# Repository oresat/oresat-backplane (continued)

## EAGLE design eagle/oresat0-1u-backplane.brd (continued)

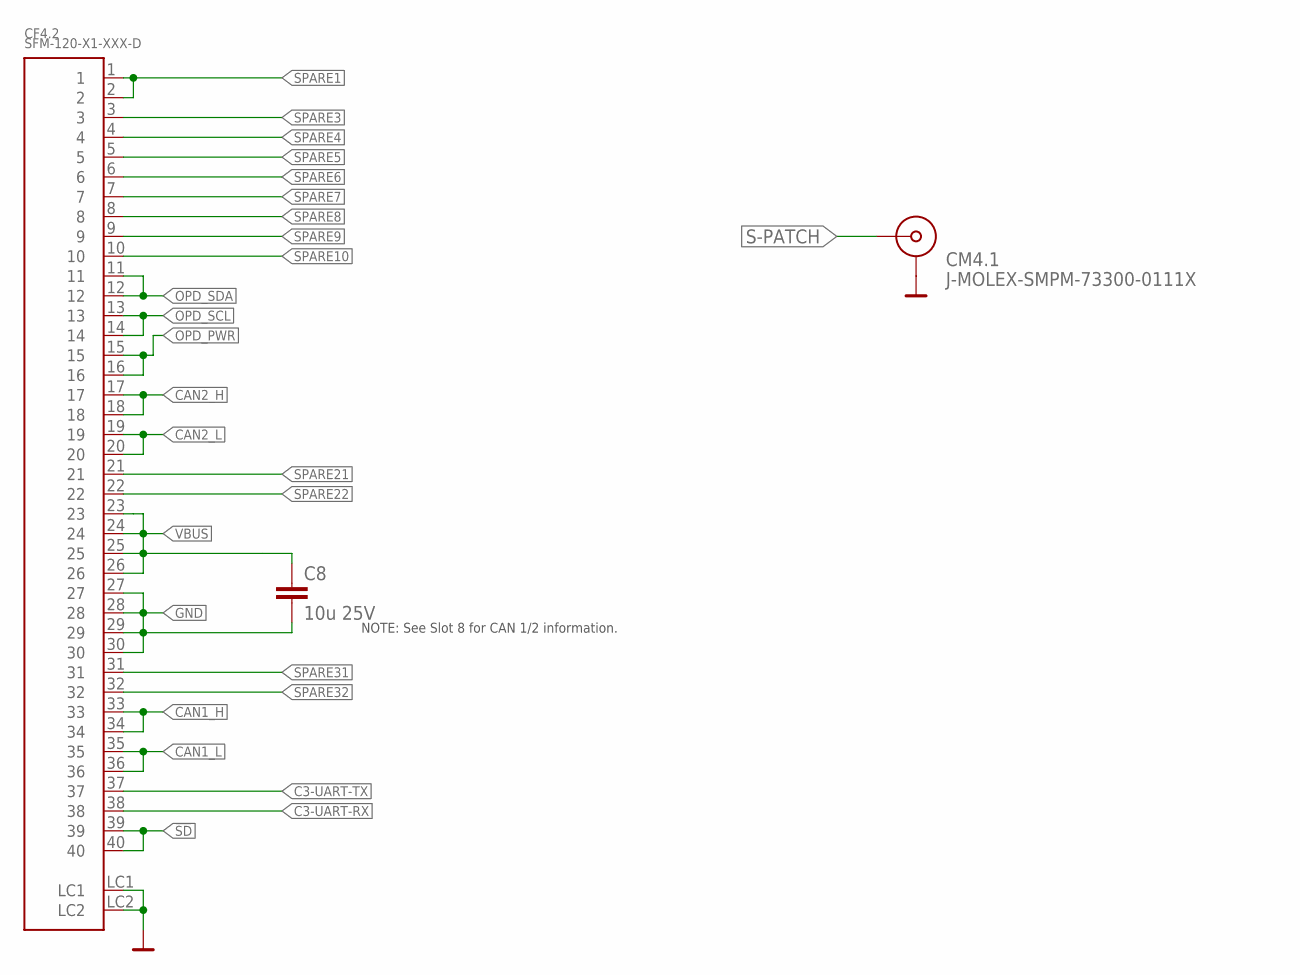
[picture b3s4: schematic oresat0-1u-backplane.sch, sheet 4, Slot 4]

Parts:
C8: 10u 25V; 1206-B
CF4.2: SFM-120-X1-XXX-D
CM4.1: J-MOLEX-SMPM-73300-0111X

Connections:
!SD: CF4.2.39, CF4.2.40; also elsewhere on the board
C3-UART-RX: CF4.2.38; also elsewhere on the board
C3-UART-TX: CF4.2.37; also elsewhere on the board
CAN1_H: CF4.2.33, CF4.2.34; also elsewhere on the board
CAN1_L: CF4.2.35, CF4.2.36; also elsewhere on the board
CAN2_H: CF4.2.17, CF4.2.18; also elsewhere on the board
CAN2_L: CF4.2.19, CF4.2.20; also elsewhere on the board
GND: C8.2, CF4.2.27, CF4.2.28, CF4.2.29, CF4.2.30, CF4.2.LC1, CF4.2.LC2, CM4.1.P$1 (SHIELD1), CM4.1.P$2 (SHIELD1), CM4.1.P$3 (SHIELD1), CM4.1.P$4 (SHIELD1); also elsewhere on the board
OPD_PWR: CF4.2.15, CF4.2.16; also elsewhere on the board
OPD_SCL: CF4.2.13, CF4.2.14; also elsewhere on the board
OPD_SDA: CF4.2.11, CF4.2.12; also elsewhere on the board
S-PATCH: CM4.1.RF-DOWN (RF); also elsewhere on the board
SPARE1: CF4.2.1, CF4.2.2; also elsewhere on the board
SPARE3: CF4.2.3; also elsewhere on the board
SPARE4: CF4.2.4; also elsewhere on the board
SPARE5: CF4.2.5; also elsewhere on the board
SPARE6: CF4.2.6; also elsewhere on the board
SPARE7: CF4.2.7; also elsewhere on the board
SPARE8: CF4.2.8; also elsewhere on the board
SPARE9: CF4.2.9; also elsewhere on the board
SPARE10: CF4.2.10; also elsewhere on the board
SPARE21: CF4.2.21; also elsewhere on the board
SPARE22: CF4.2.22; also elsewhere on the board
SPARE31: CF4.2.31; also elsewhere on the board
SPARE32: CF4.2.32; also elsewhere on the board
VBUS: C8.1, CF4.2.23, CF4.2.24, CF4.2.25, CF4.2.26; also elsewhere on the board

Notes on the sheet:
NOTE: See Slot 8 for CAN 1/2 information.

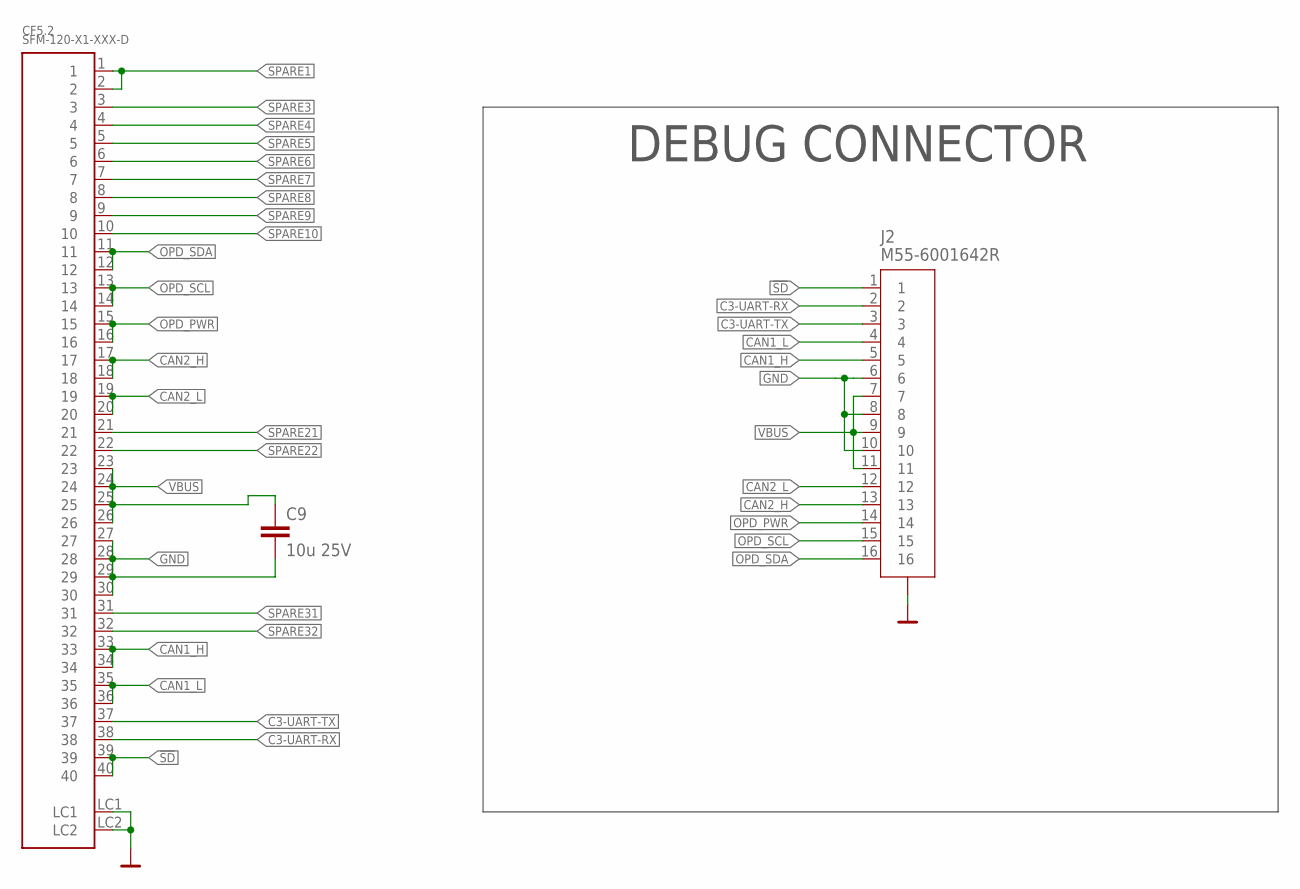
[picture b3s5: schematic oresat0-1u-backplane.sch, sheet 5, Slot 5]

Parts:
C9: 10u 25V; 1206-B
CF5.2: SFM-120-X1-XXX-D
J2: M55-6001642R; CONN_M55-6001642R_HRW

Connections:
!SD: CF5.2.39, CF5.2.40, J2.1; also elsewhere on the board
C3-UART-RX: CF5.2.38, J2.2; also elsewhere on the board
C3-UART-TX: CF5.2.37, J2.3; also elsewhere on the board
CAN1_H: CF5.2.33, CF5.2.34, J2.5; also elsewhere on the board
CAN1_L: CF5.2.35, CF5.2.36, J2.4; also elsewhere on the board
CAN2_H: CF5.2.17, CF5.2.18, J2.13; also elsewhere on the board
CAN2_L: CF5.2.19, CF5.2.20, J2.12; also elsewhere on the board
GND: C9.2, CF5.2.27, CF5.2.28, CF5.2.29, CF5.2.30, CF5.2.LC1, CF5.2.LC2, J2.6, J2.8, J2.10, J2.19 (17), J2.20 (17), J2.21 (17), J2.22 (17); also elsewhere on the board
OPD_PWR: CF5.2.15, CF5.2.16, J2.14; also elsewhere on the board
OPD_SCL: CF5.2.13, CF5.2.14, J2.15; also elsewhere on the board
OPD_SDA: CF5.2.11, CF5.2.12, J2.16; also elsewhere on the board
SPARE1: CF5.2.1, CF5.2.2; also elsewhere on the board
SPARE3: CF5.2.3; also elsewhere on the board
SPARE4: CF5.2.4; also elsewhere on the board
SPARE5: CF5.2.5; also elsewhere on the board
SPARE6: CF5.2.6; also elsewhere on the board
SPARE7: CF5.2.7; also elsewhere on the board
SPARE8: CF5.2.8; also elsewhere on the board
SPARE9: CF5.2.9; also elsewhere on the board
SPARE10: CF5.2.10; also elsewhere on the board
SPARE21: CF5.2.21; also elsewhere on the board
SPARE22: CF5.2.22; also elsewhere on the board
SPARE31: CF5.2.31; also elsewhere on the board
SPARE32: CF5.2.32; also elsewhere on the board
VBUS: C9.1, CF5.2.23, CF5.2.24, CF5.2.25, CF5.2.26, J2.7, J2.9, J2.11; also elsewhere on the board

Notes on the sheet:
DEBUG CONNECTOR

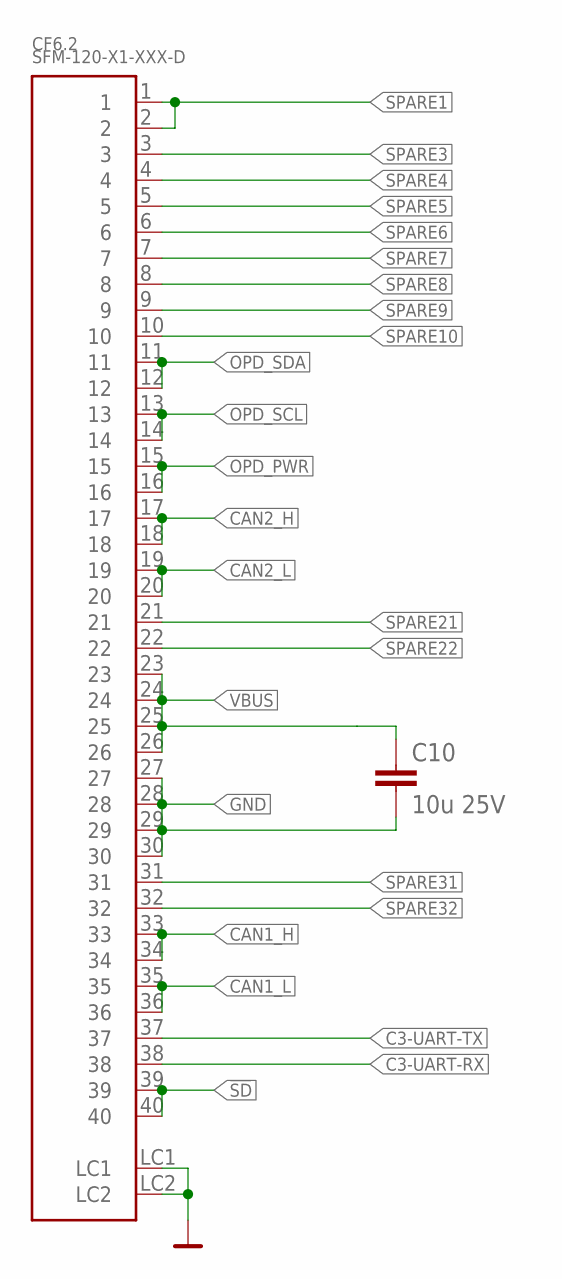
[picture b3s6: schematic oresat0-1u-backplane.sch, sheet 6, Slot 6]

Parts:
C10: 10u 25V; 1206-B
CF6.2: SFM-120-X1-XXX-D

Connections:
!SD: CF6.2.39, CF6.2.40; also elsewhere on the board
C3-UART-RX: CF6.2.38; also elsewhere on the board
C3-UART-TX: CF6.2.37; also elsewhere on the board
CAN1_H: CF6.2.33, CF6.2.34; also elsewhere on the board
CAN1_L: CF6.2.35, CF6.2.36; also elsewhere on the board
CAN2_H: CF6.2.17, CF6.2.18; also elsewhere on the board
CAN2_L: CF6.2.19, CF6.2.20; also elsewhere on the board
GND: C10.2, CF6.2.27, CF6.2.28, CF6.2.29, CF6.2.30, CF6.2.LC1, CF6.2.LC2; also elsewhere on the board
OPD_PWR: CF6.2.15, CF6.2.16; also elsewhere on the board
OPD_SCL: CF6.2.13, CF6.2.14; also elsewhere on the board
OPD_SDA: CF6.2.11, CF6.2.12; also elsewhere on the board
SPARE1: CF6.2.1, CF6.2.2; also elsewhere on the board
SPARE3: CF6.2.3; also elsewhere on the board
SPARE4: CF6.2.4; also elsewhere on the board
SPARE5: CF6.2.5; also elsewhere on the board
SPARE6: CF6.2.6; also elsewhere on the board
SPARE7: CF6.2.7; also elsewhere on the board
SPARE8: CF6.2.8; also elsewhere on the board
SPARE9: CF6.2.9; also elsewhere on the board
SPARE10: CF6.2.10; also elsewhere on the board
SPARE21: CF6.2.21; also elsewhere on the board
SPARE22: CF6.2.22; also elsewhere on the board
SPARE31: CF6.2.31; also elsewhere on the board
SPARE32: CF6.2.32; also elsewhere on the board
VBUS: C10.1, CF6.2.23, CF6.2.24, CF6.2.25, CF6.2.26; also elsewhere on the board

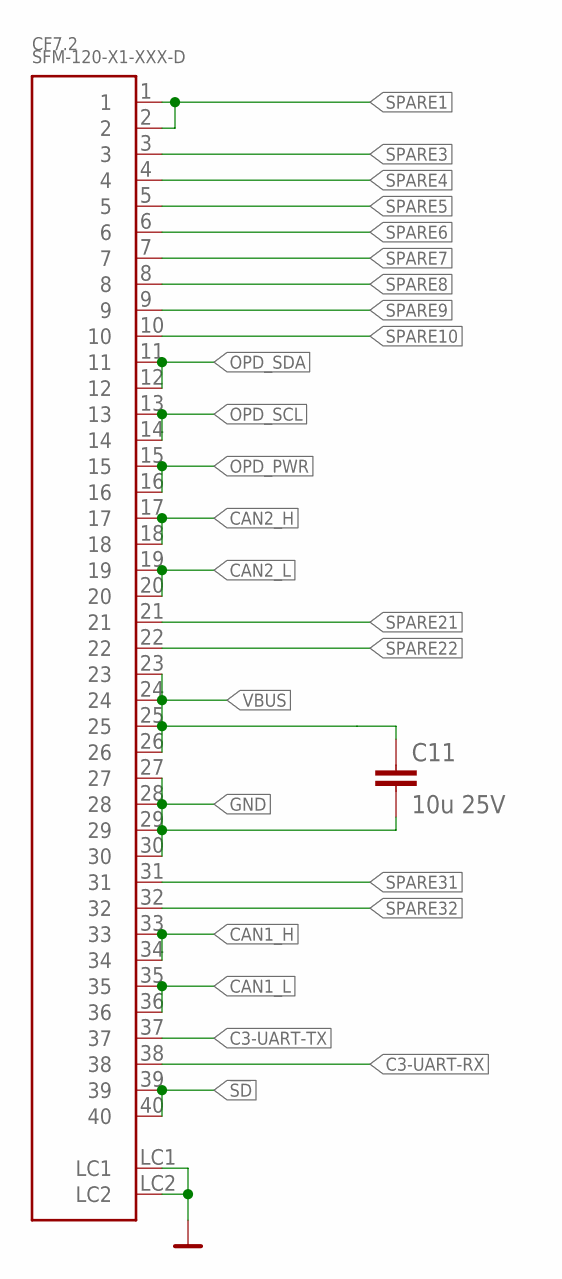
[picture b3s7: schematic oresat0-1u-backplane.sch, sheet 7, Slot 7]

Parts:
C11: 10u 25V; 1206-B
CF7.2: SFM-120-X1-XXX-D

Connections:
!SD: CF7.2.39, CF7.2.40; also elsewhere on the board
C3-UART-RX: CF7.2.38; also elsewhere on the board
C3-UART-TX: CF7.2.37; also elsewhere on the board
CAN1_H: CF7.2.33, CF7.2.34; also elsewhere on the board
CAN1_L: CF7.2.35, CF7.2.36; also elsewhere on the board
CAN2_H: CF7.2.17, CF7.2.18; also elsewhere on the board
CAN2_L: CF7.2.19, CF7.2.20; also elsewhere on the board
GND: C11.2, CF7.2.27, CF7.2.28, CF7.2.29, CF7.2.30, CF7.2.LC1, CF7.2.LC2; also elsewhere on the board
OPD_PWR: CF7.2.15, CF7.2.16; also elsewhere on the board
OPD_SCL: CF7.2.13, CF7.2.14; also elsewhere on the board
OPD_SDA: CF7.2.11, CF7.2.12; also elsewhere on the board
SPARE1: CF7.2.1, CF7.2.2; also elsewhere on the board
SPARE3: CF7.2.3; also elsewhere on the board
SPARE4: CF7.2.4; also elsewhere on the board
SPARE5: CF7.2.5; also elsewhere on the board
SPARE6: CF7.2.6; also elsewhere on the board
SPARE7: CF7.2.7; also elsewhere on the board
SPARE8: CF7.2.8; also elsewhere on the board
SPARE9: CF7.2.9; also elsewhere on the board
SPARE10: CF7.2.10; also elsewhere on the board
SPARE21: CF7.2.21; also elsewhere on the board
SPARE22: CF7.2.22; also elsewhere on the board
SPARE31: CF7.2.31; also elsewhere on the board
SPARE32: CF7.2.32; also elsewhere on the board
VBUS: C11.1, CF7.2.23, CF7.2.24, CF7.2.25, CF7.2.26; also elsewhere on the board

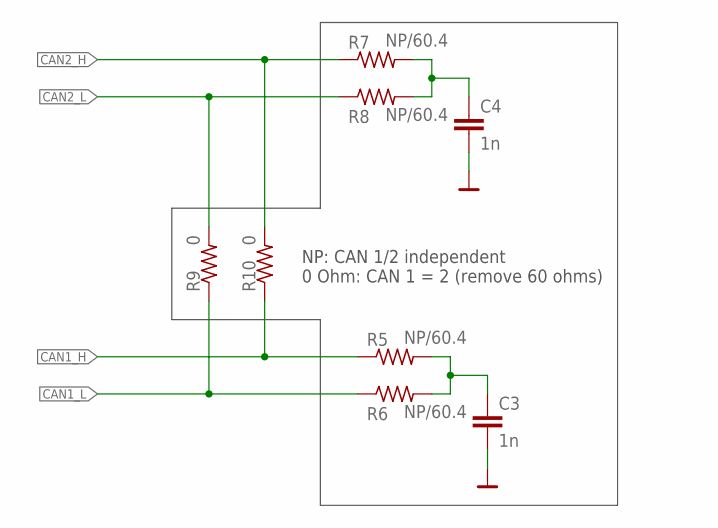
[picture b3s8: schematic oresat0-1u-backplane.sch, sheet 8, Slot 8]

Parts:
C3, C4: 1n; .0603-C-NOSILK
R5, R6, R7, R8: NP/60.4; 1206-C
R9, R10: 0; .0603-B-NOSILK

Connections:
CAN1_H: R5.1, R10.1; also elsewhere on the board
CAN1_L: R6.1, R9.1; also elsewhere on the board
CAN2_H: R7.1, R10.2; also elsewhere on the board
CAN2_L: R8.1, R9.2; also elsewhere on the board
GND: C3.2, C4.2; also elsewhere on the board
unnamed: C4.1, R7.2, R8.2
unnamed: C3.1, R5.2, R6.2

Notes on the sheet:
NP: CAN 1/2 independent 0 Ohm: CAN 1 = 2 (remove 60 ohms)

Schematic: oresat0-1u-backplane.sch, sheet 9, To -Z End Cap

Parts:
CM8: U.FL-R-SMA; U.FL-R-SMT
J1: 5-104196-5

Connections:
GND: CM8.2, CM8.3, J1.HD1 (HD), J1.HD2 (HD), J1.HD3 (HD); also elsewhere on the board
S-PATCH: CM8.1; also elsewhere on the board
SPARE1: J1.19, J1.20; also elsewhere on the board
SPARE3: J1.18; also elsewhere on the board
SPARE4: J1.17; also elsewhere on the board
SPARE5: J1.16; also elsewhere on the board
SPARE6: J1.15; also elsewhere on the board
SPARE7: J1.14; also elsewhere on the board
SPARE8: J1.13; also elsewhere on the board
SPARE9: J1.12; also elsewhere on the board
SPARE10: J1.11; also elsewhere on the board

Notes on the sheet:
-Z End Cap Connector

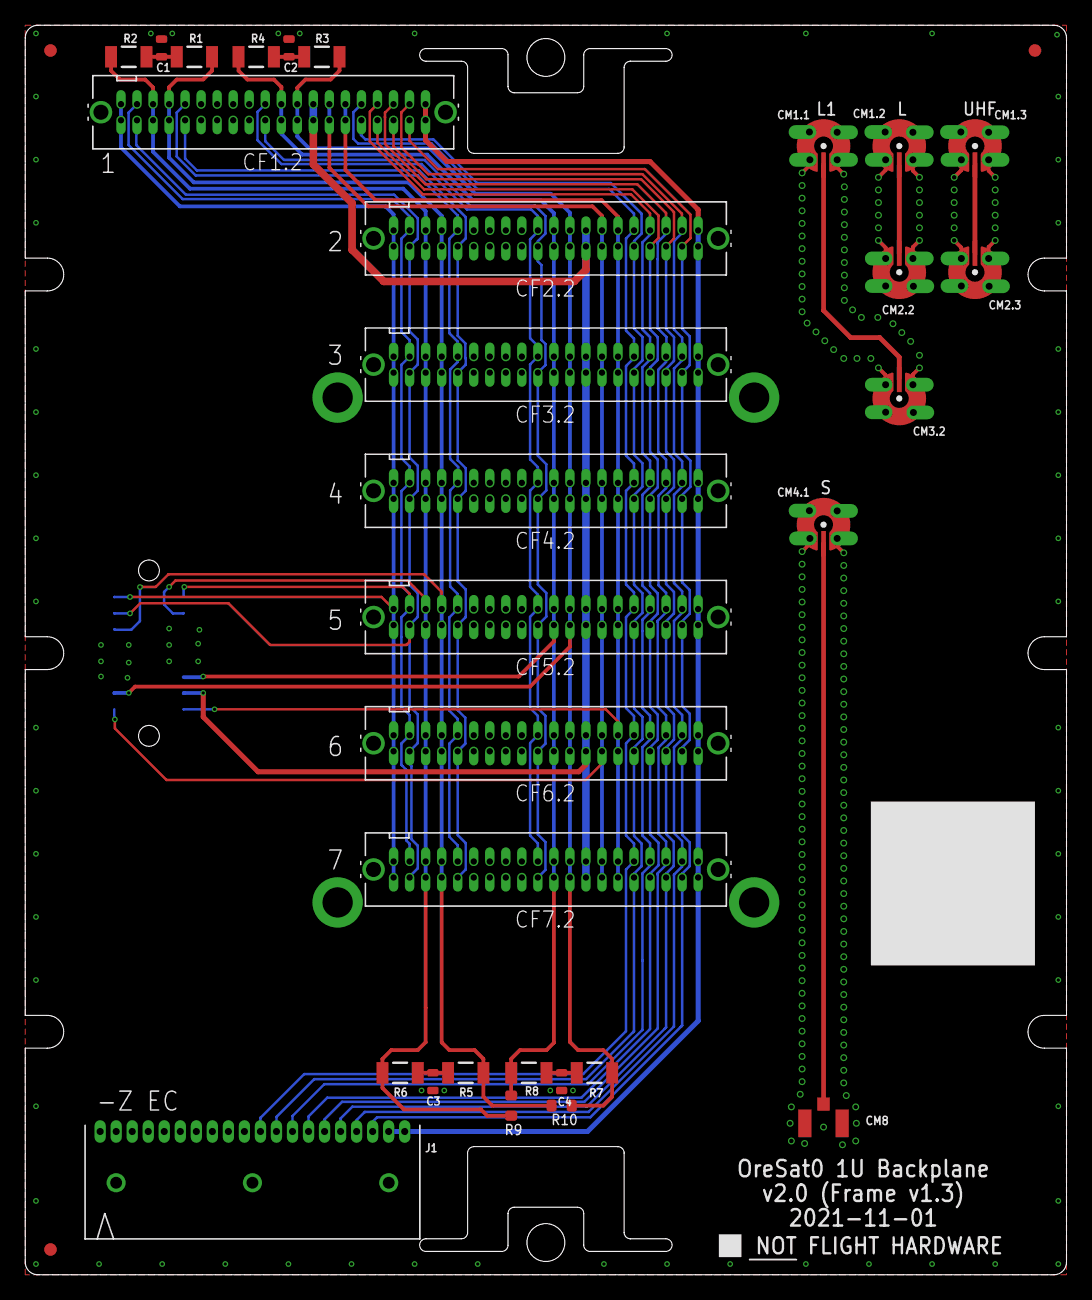
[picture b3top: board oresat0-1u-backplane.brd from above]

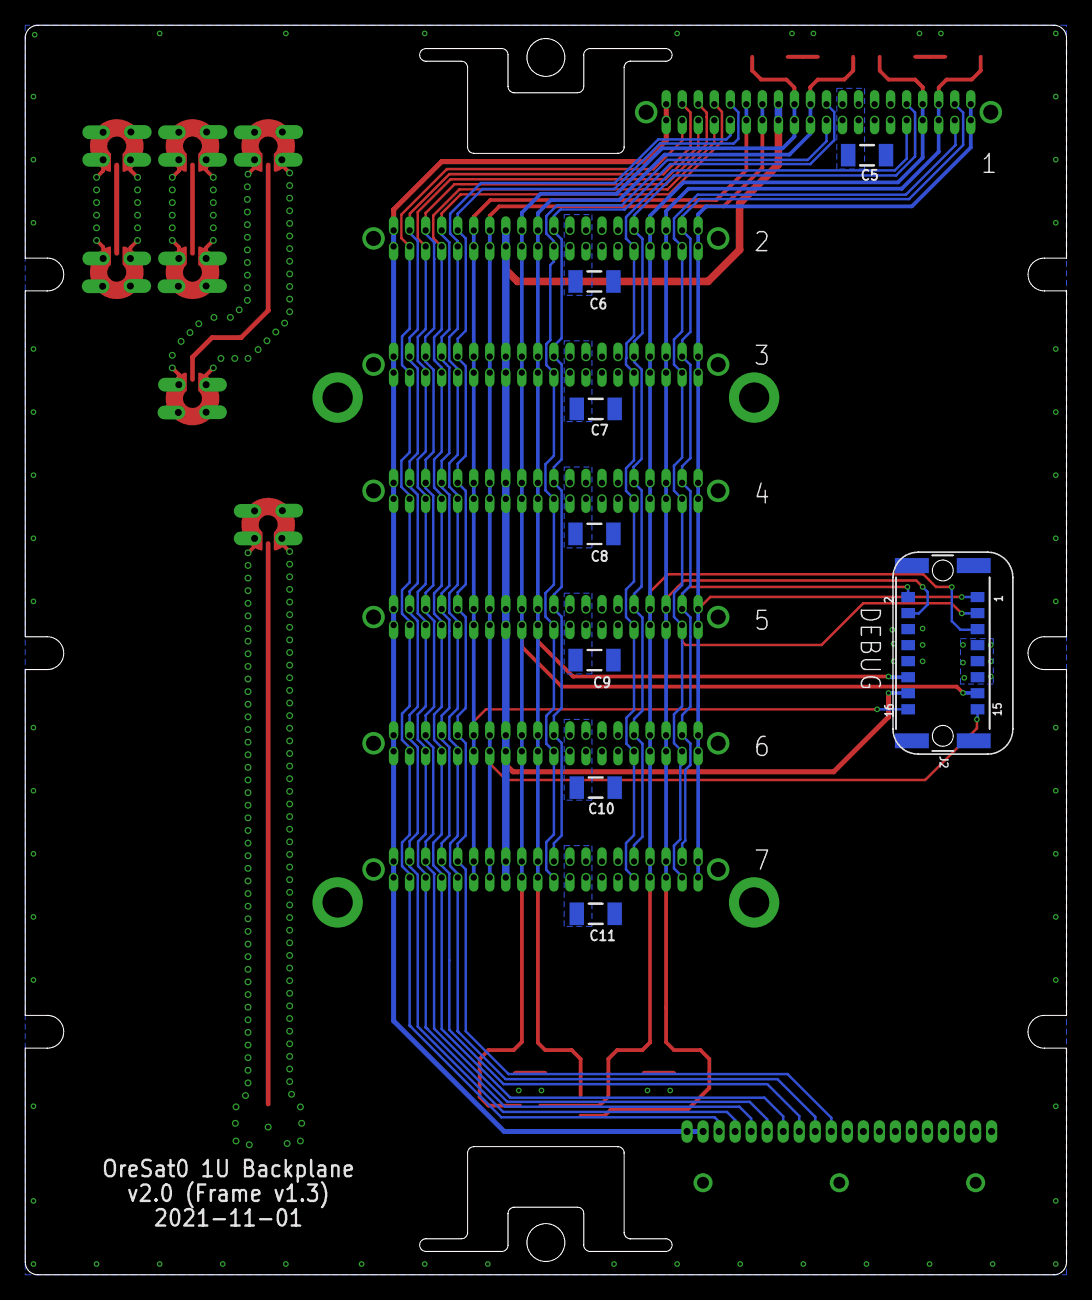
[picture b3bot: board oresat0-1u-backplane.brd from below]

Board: 4 copper layers, 82.5 x 99.0 mm, 42 parts (8 on the bottom side), 33 nets.

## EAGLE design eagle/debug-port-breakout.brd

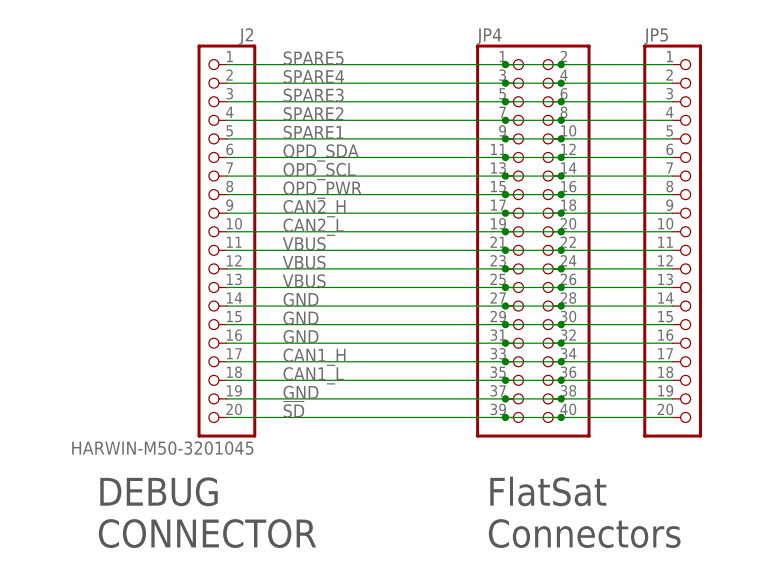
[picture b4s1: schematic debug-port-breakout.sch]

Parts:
J2: HARWIN-M50-3201045
JP4: PINHD-2X20; 2X20
JP5: PINHD-1X20; 1X20

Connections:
!SD: J2.20, JP4.39, JP4.40, JP5.20
CAN1_H: J2.17, JP4.33, JP4.34, JP5.17
CAN1_L: J2.18, JP4.35, JP4.36, JP5.18
CAN2_H: J2.9, JP4.17, JP4.18, JP5.9
CAN2_L: J2.10, JP4.19, JP4.20, JP5.10
GND: J2.14, J2.15, J2.16, J2.19, JP4.27, JP4.28, JP4.29, JP4.30, JP4.31, JP4.32, JP4.37, JP4.38, JP5.14, JP5.15, JP5.16, JP5.19
OPD_PWR: J2.8, JP4.15, JP4.16, JP5.8
OPD_SCL: J2.7, JP4.13, JP4.14, JP5.7
OPD_SDA: J2.6, JP4.11, JP4.12, JP5.6
SPARE1: J2.5, JP4.9, JP4.10, JP5.5
SPARE2: J2.4, JP4.7, JP4.8, JP5.4
SPARE3: J2.3, JP4.5, JP4.6, JP5.3
SPARE4: J2.2, JP4.3, JP4.4, JP5.2
SPARE5: J2.1, JP4.1, JP4.2, JP5.1
VBUS: J2.11, J2.12, J2.13, JP4.21, JP4.22, JP4.23, JP4.24, JP4.25, JP4.26, JP5.11, JP5.12, JP5.13

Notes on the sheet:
DEBUG CONNECTOR
FlatSat Connectors

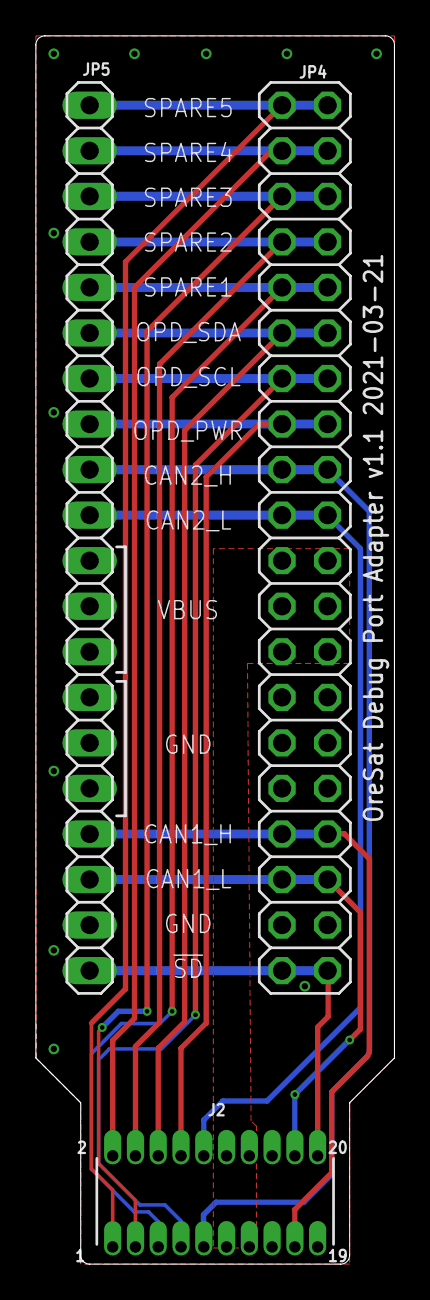
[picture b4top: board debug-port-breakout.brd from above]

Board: 2 copper layers, 20.0 x 68.5 mm, 3 parts (0 on the bottom side), 15 nets.

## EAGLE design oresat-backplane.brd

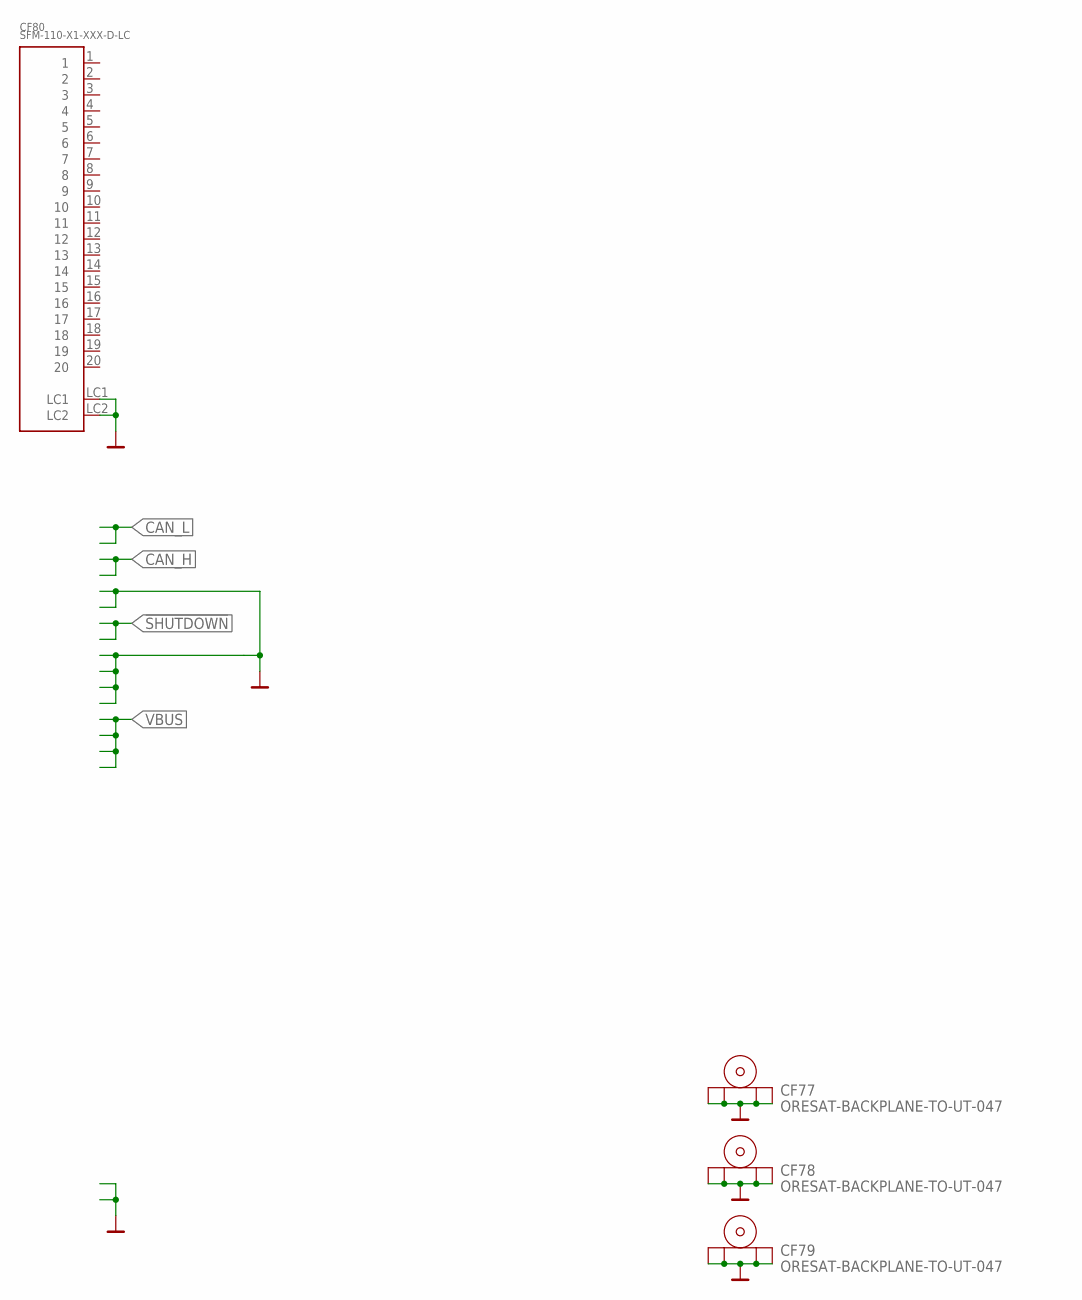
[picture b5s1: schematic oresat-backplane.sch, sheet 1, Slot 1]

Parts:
CF77, CF78, CF79: ORESAT-BACKPLANE-TO-UT-047; TEST
CF80: SFM-110-X1-XXX-D-LC

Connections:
GND: CF77.GND@1 (SHIELD), CF77.GND@2 (SHIELD1), CF77.GND@3 (SHIELD2), CF77.GND@4 (SHIELD3), CF78.GND@1 (SHIELD), CF78.GND@2 (SHIELD1), CF78.GND@3 (SHIELD2), CF78.GND@4 (SHIELD3), CF79.GND@1 (SHIELD), CF79.GND@2 (SHIELD1), CF79.GND@3 (SHIELD2), CF79.GND@4 (SHIELD3), CF80.LC1, CF80.LC2; also elsewhere on the board

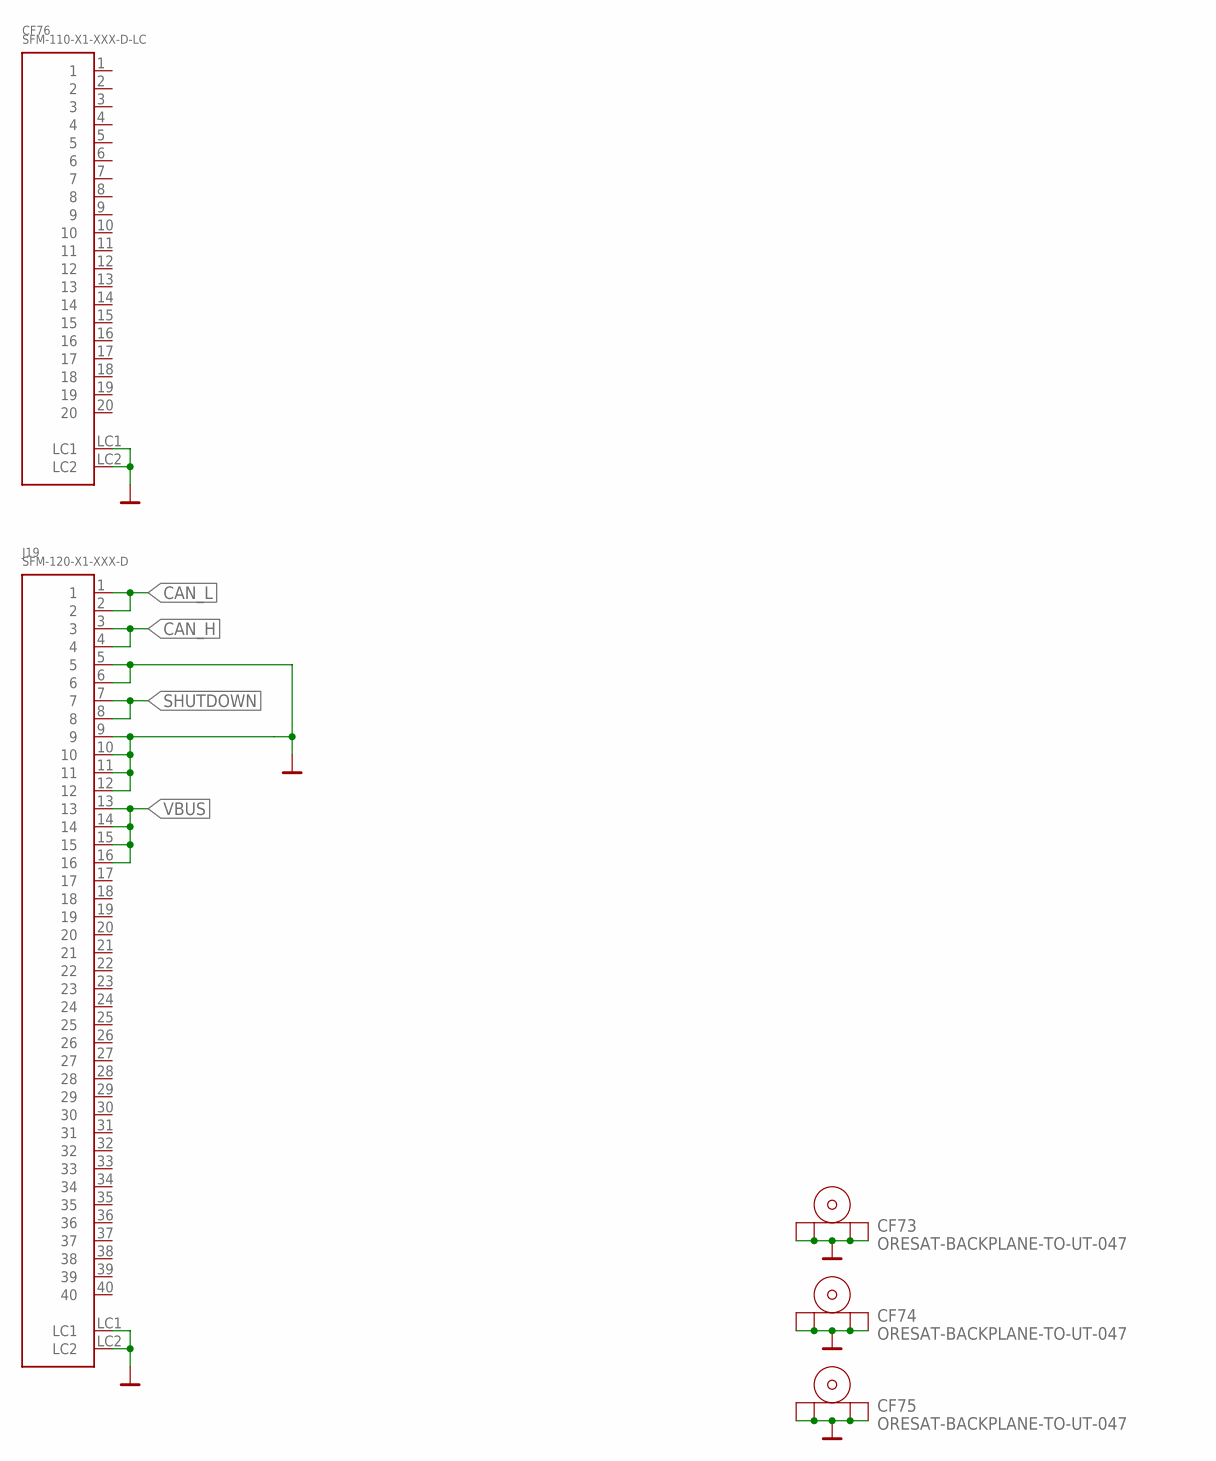
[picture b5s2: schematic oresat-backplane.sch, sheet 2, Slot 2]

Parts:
CF73, CF74, CF75: ORESAT-BACKPLANE-TO-UT-047; TEST
CF76: SFM-110-X1-XXX-D-LC
J19: SFM-120-X1-XXX-D

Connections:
!SHUTDOWN: J19.7, J19.8; also elsewhere on the board
CAN_H: J19.3, J19.4; also elsewhere on the board
CAN_L: J19.1, J19.2; also elsewhere on the board
GND: CF73.GND@1 (SHIELD), CF73.GND@2 (SHIELD1), CF73.GND@3 (SHIELD2), CF73.GND@4 (SHIELD3), CF74.GND@1 (SHIELD), CF74.GND@2 (SHIELD1), CF74.GND@3 (SHIELD2), CF74.GND@4 (SHIELD3), CF75.GND@1 (SHIELD), CF75.GND@2 (SHIELD1), CF75.GND@3 (SHIELD2), CF75.GND@4 (SHIELD3), CF76.LC1, CF76.LC2, J19.5, J19.6, J19.9, J19.10, J19.11, J19.12, J19.LC1, J19.LC2; also elsewhere on the board
VBUS: J19.13, J19.14, J19.15, J19.16; also elsewhere on the board

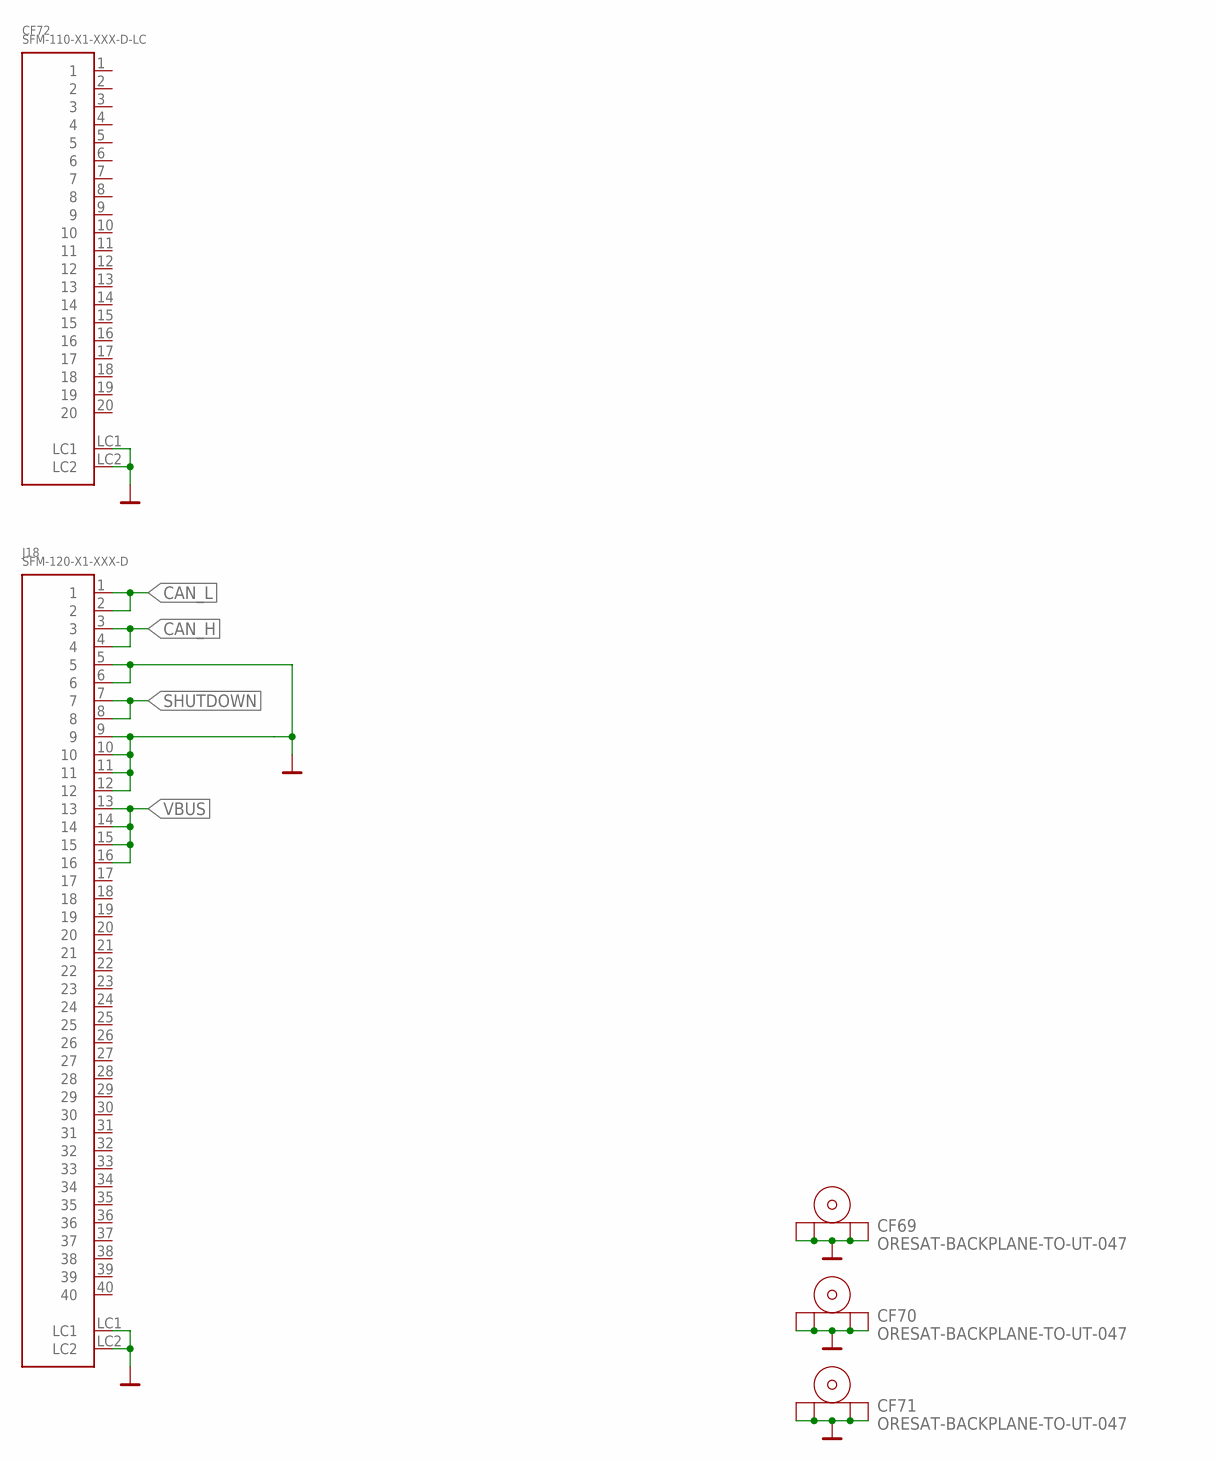
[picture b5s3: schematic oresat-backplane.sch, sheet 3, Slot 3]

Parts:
CF69, CF70, CF71: ORESAT-BACKPLANE-TO-UT-047; TEST
CF72: SFM-110-X1-XXX-D-LC
J18: SFM-120-X1-XXX-D

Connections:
!SHUTDOWN: J18.7, J18.8; also elsewhere on the board
CAN_H: J18.3, J18.4; also elsewhere on the board
CAN_L: J18.1, J18.2; also elsewhere on the board
GND: CF69.GND@1 (SHIELD), CF69.GND@2 (SHIELD1), CF69.GND@3 (SHIELD2), CF69.GND@4 (SHIELD3), CF70.GND@1 (SHIELD), CF70.GND@2 (SHIELD1), CF70.GND@3 (SHIELD2), CF70.GND@4 (SHIELD3), CF71.GND@1 (SHIELD), CF71.GND@2 (SHIELD1), CF71.GND@3 (SHIELD2), CF71.GND@4 (SHIELD3), CF72.LC1, CF72.LC2, J18.5, J18.6, J18.9, J18.10, J18.11, J18.12, J18.LC1, J18.LC2; also elsewhere on the board
VBUS: J18.13, J18.14, J18.15, J18.16; also elsewhere on the board

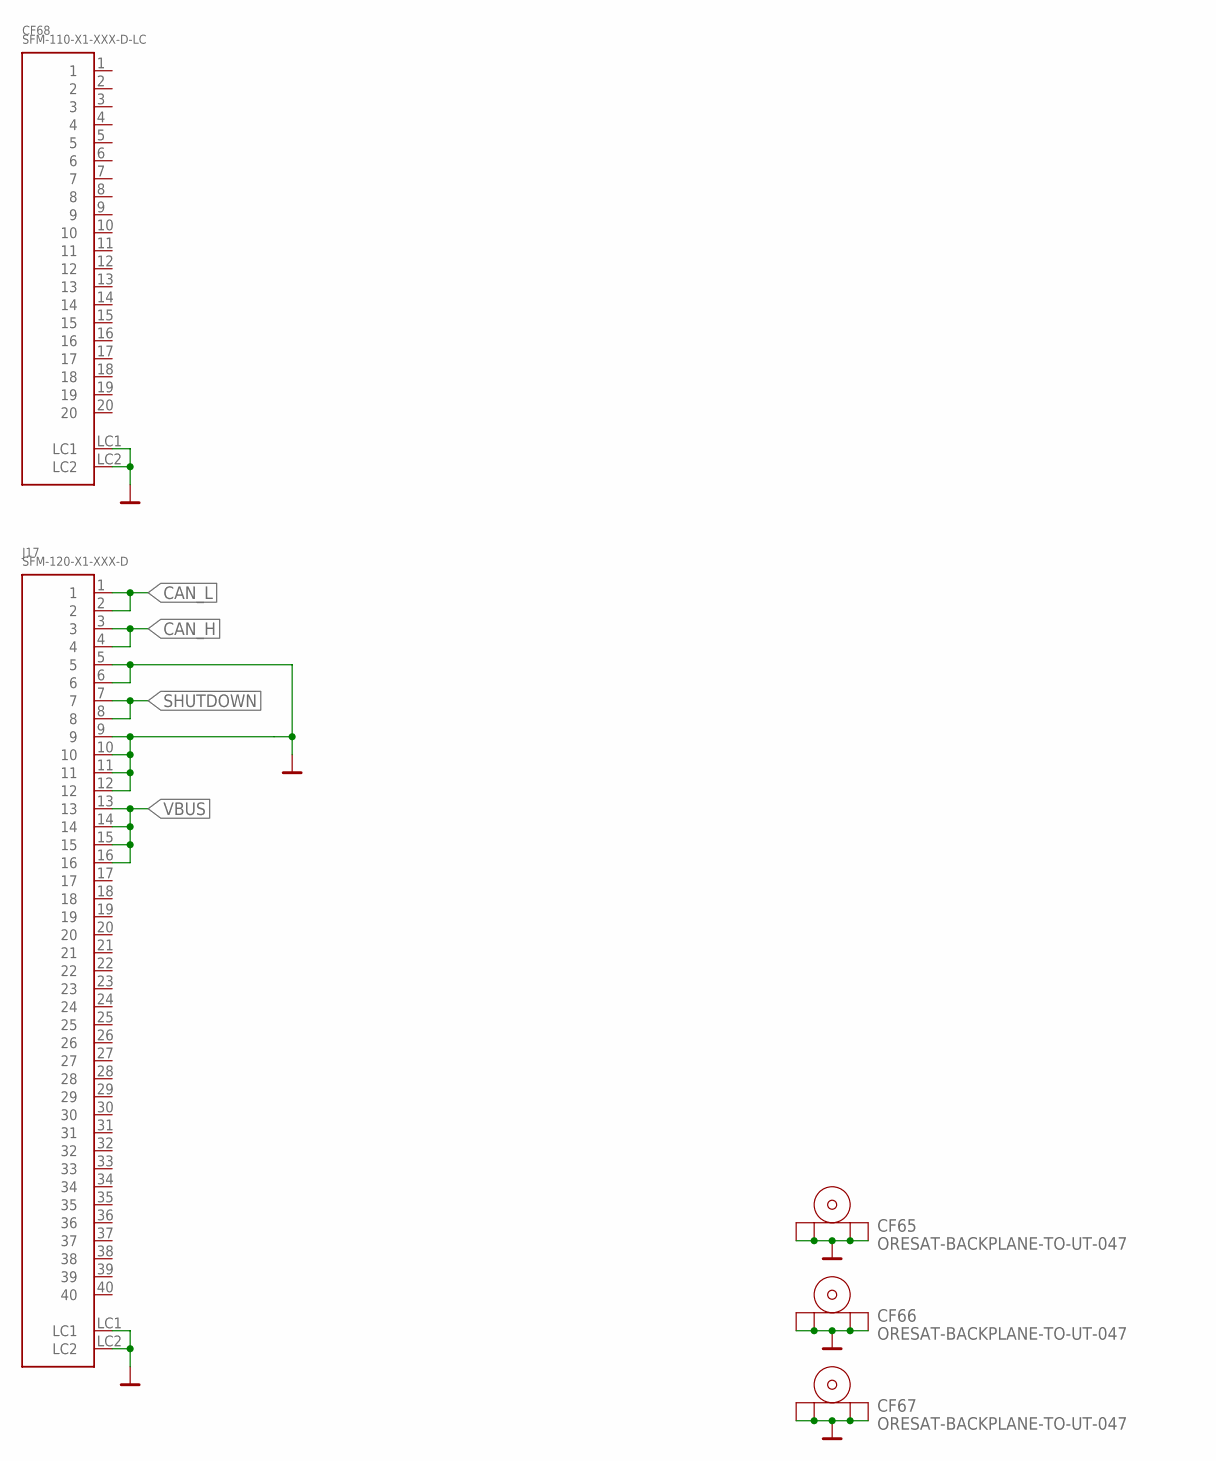
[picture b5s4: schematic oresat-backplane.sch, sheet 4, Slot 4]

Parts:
CF65, CF66, CF67: ORESAT-BACKPLANE-TO-UT-047; TEST
CF68: SFM-110-X1-XXX-D-LC
J17: SFM-120-X1-XXX-D

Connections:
!SHUTDOWN: J17.7, J17.8; also elsewhere on the board
CAN_H: J17.3, J17.4; also elsewhere on the board
CAN_L: J17.1, J17.2; also elsewhere on the board
GND: CF65.GND@1 (SHIELD), CF65.GND@2 (SHIELD1), CF65.GND@3 (SHIELD2), CF65.GND@4 (SHIELD3), CF66.GND@1 (SHIELD), CF66.GND@2 (SHIELD1), CF66.GND@3 (SHIELD2), CF66.GND@4 (SHIELD3), CF67.GND@1 (SHIELD), CF67.GND@2 (SHIELD1), CF67.GND@3 (SHIELD2), CF67.GND@4 (SHIELD3), CF68.LC1, CF68.LC2, J17.5, J17.6, J17.9, J17.10, J17.11, J17.12, J17.LC1, J17.LC2; also elsewhere on the board
VBUS: J17.13, J17.14, J17.15, J17.16; also elsewhere on the board
